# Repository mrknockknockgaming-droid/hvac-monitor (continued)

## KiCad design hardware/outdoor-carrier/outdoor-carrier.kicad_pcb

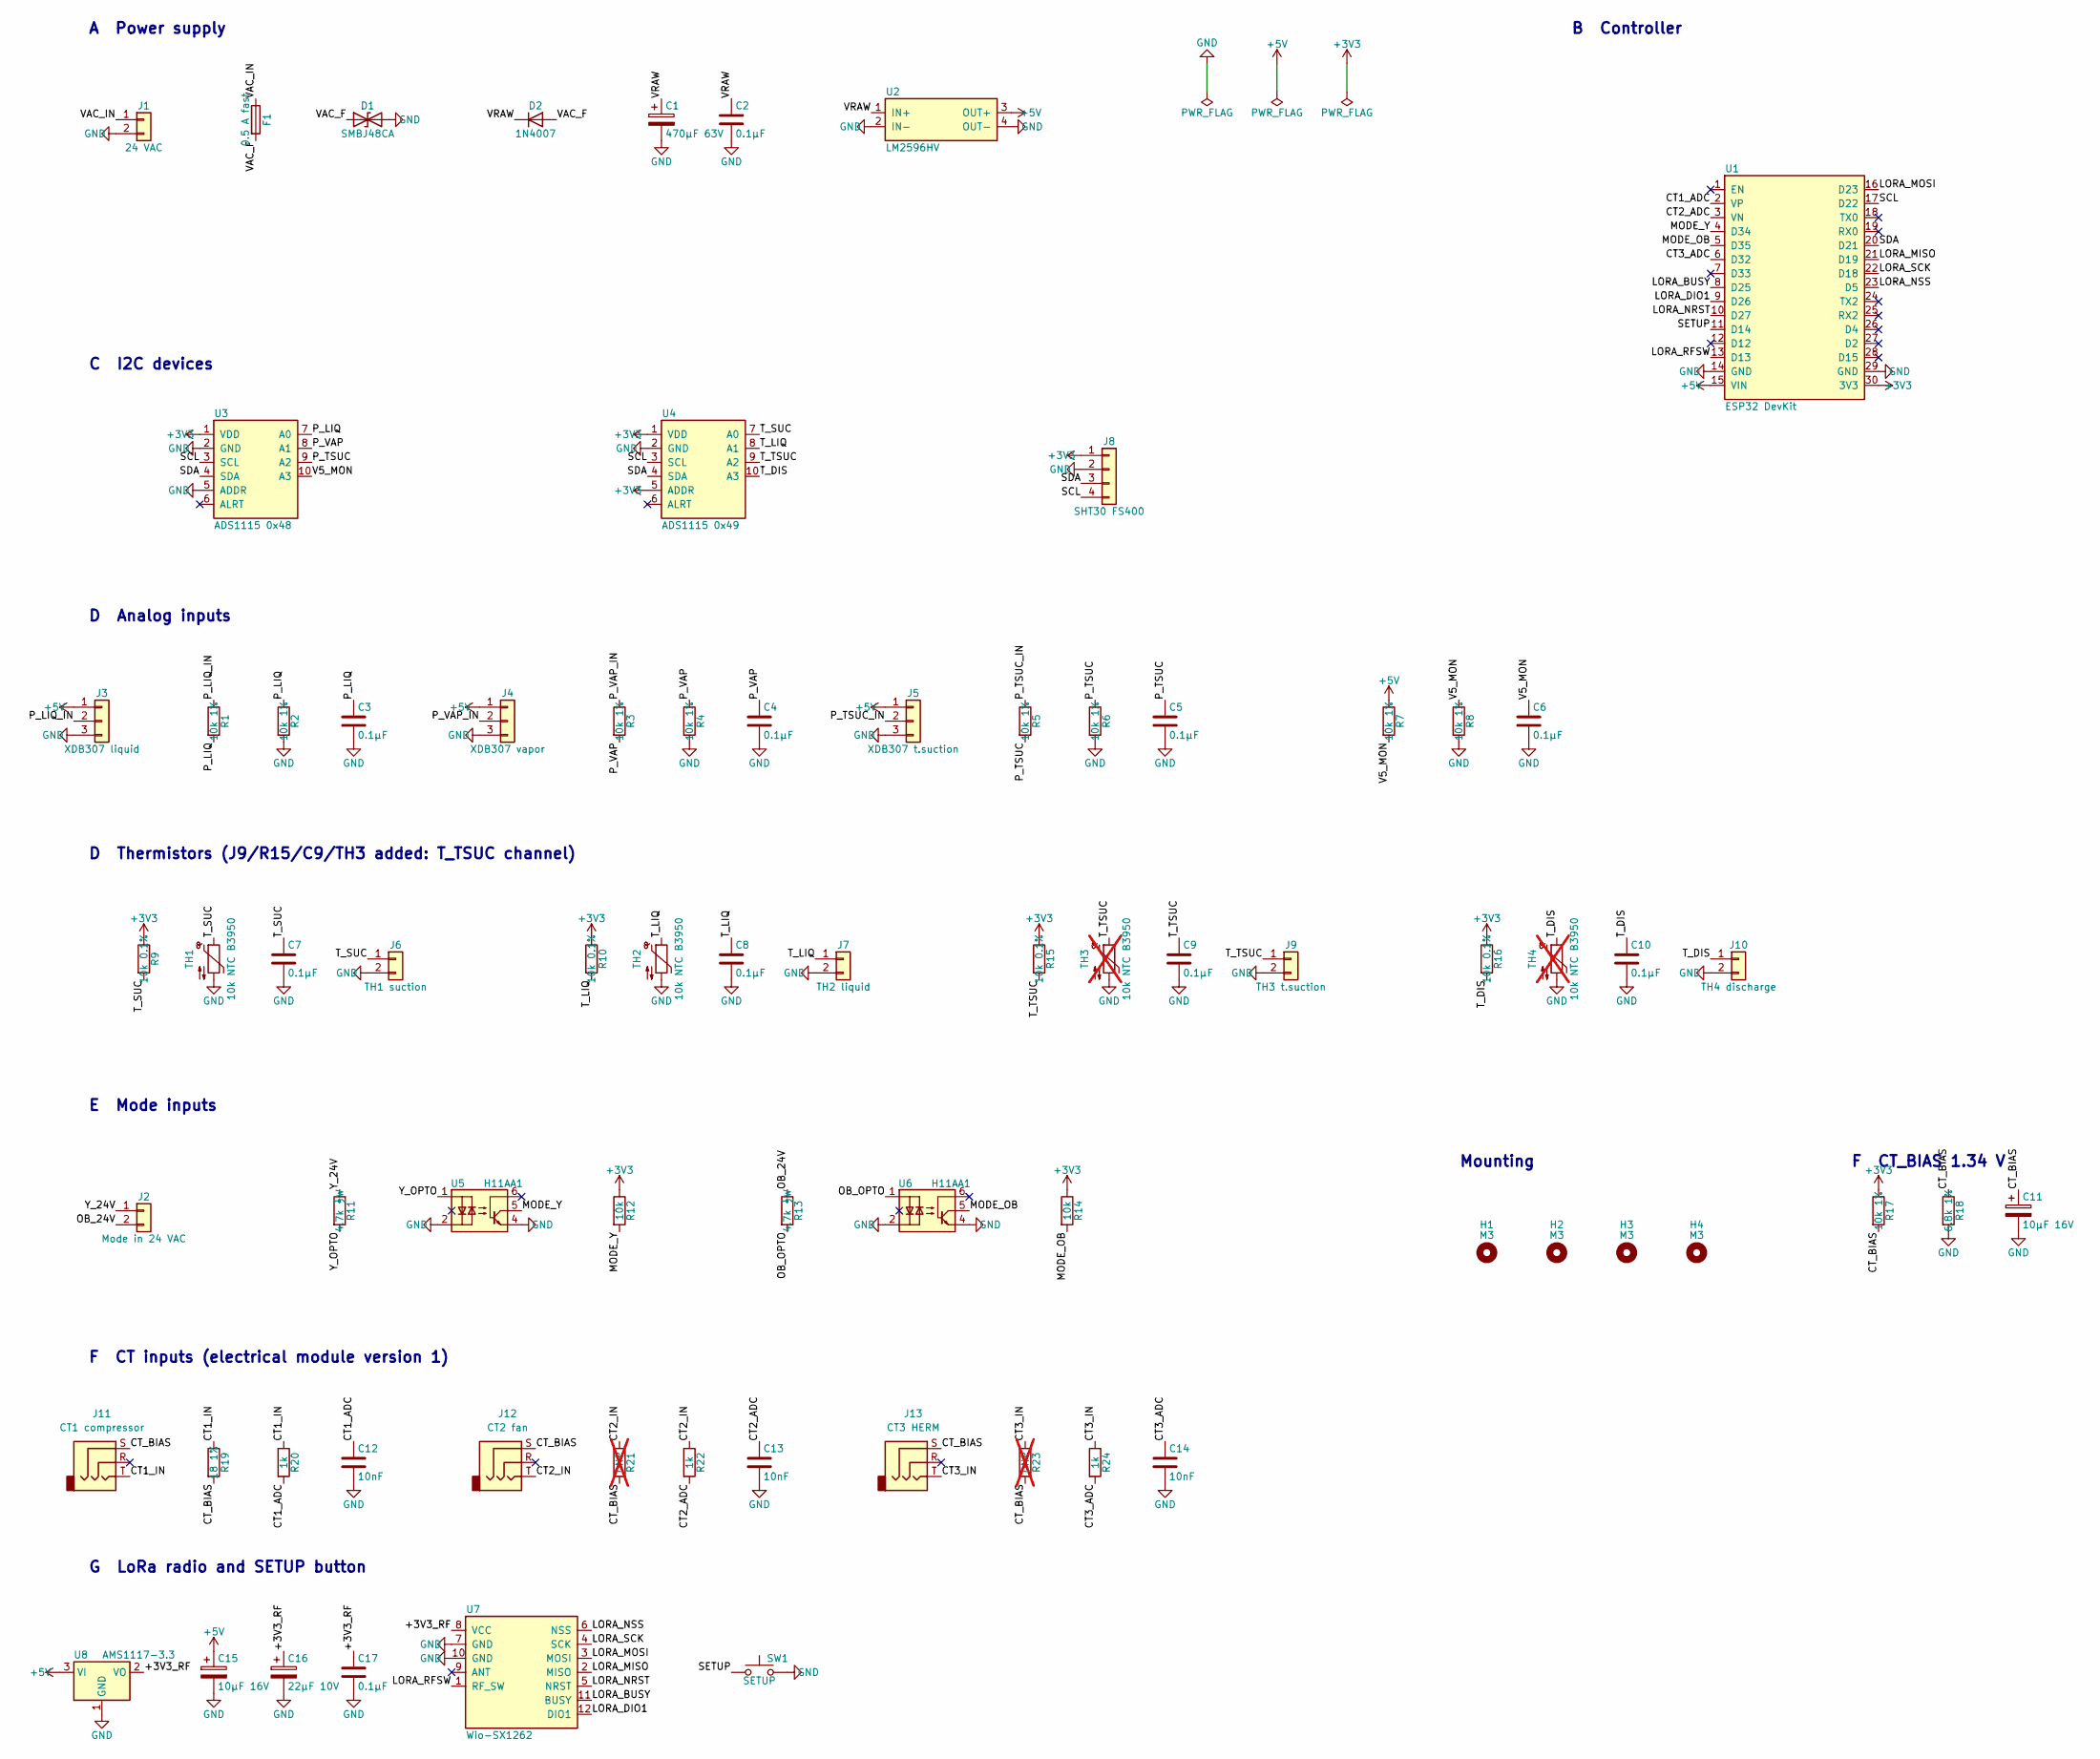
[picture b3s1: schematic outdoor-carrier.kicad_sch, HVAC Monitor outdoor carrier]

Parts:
C1: 470µF 63V; CP_Radial_D10.0mm_P5.00mm
C2, C3, C4, C5, C6, C7, C8, C9, C10, C17: 0.1µF; C_Disc_D5.0mm_W2.5mm_P2.50mm
C11, C15: 10µF 16V; CP_Radial_D5.0mm_P2.00mm
C12, C13, C14: 10nF; C_0805_2012Metric_Pad1.18x1.45mm_HandSolder
C16: 22µF 10V; CP_Radial_D5.0mm_P2.00mm
D1: SMBJ48CA; D_SMB_Handsoldering
D2: 1N4007; D_DO-41_SOD81_P10.16mm_Horizontal
F1: 0.5 A fast; Fuseholder_Clip-5x20mm_Littelfuse_111_Inline_P20.00x5.00mm_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
H1, H2, H3, H4: M3; MountingHole_3.2mm_M3_DIN965
J1: 24 VAC; PhoenixContact_MC_1,5_2-G-5.08_1x02_P5.08mm_Horizontal
J2: Mode in 24 VAC; PhoenixContact_MC_1,5_2-G-5.08_1x02_P5.08mm_Horizontal
J3: XDB307 liquid; JST_XH_B3B-XH-A_1x03_P2.50mm_Vertical
J4: XDB307 vapor; JST_XH_B3B-XH-A_1x03_P2.50mm_Vertical
J5: XDB307 t.suction; JST_XH_B3B-XH-A_1x03_P2.50mm_Vertical
J6: TH1 suction; JST_XH_B2B-XH-A_1x02_P2.50mm_Vertical
J7: TH2 liquid; JST_XH_B2B-XH-A_1x02_P2.50mm_Vertical
J8: SHT30 FS400; PhoenixContact_MC_1,5_4-G-5.08_1x04_P5.08mm_Horizontal
J9: TH3 t.suction; JST_XH_B2B-XH-A_1x02_P2.50mm_Vertical
J10: TH4 discharge; JST_XH_B2B-XH-A_1x02_P2.50mm_Vertical
J11: CT1 compressor; Jack_3.5mm_CUI_SJ1-3523N_Horizontal_EdgeTrim
J12: CT2 fan; Jack_3.5mm_CUI_SJ1-3523N_Horizontal_EdgeTrim
J13: CT3 HERM; Jack_3.5mm_CUI_SJ1-3523N_Horizontal_EdgeTrim
R1, R2, R3, R4, R5, R6, R7, R8: 10k 1%; R_Axial_DIN0207_L6.3mm_D2.5mm_P10.16mm_Horizontal
R9, R10, R15, R16: 10k 0.1%; R_Axial_DIN0207_L6.3mm_D2.5mm_P10.16mm_Horizontal
R11, R13: 4.7k ½W; R_Axial_DIN0309_L9.0mm_D3.2mm_P12.70mm_Horizontal
R12, R14: 10k; R_Axial_DIN0207_L6.3mm_D2.5mm_P10.16mm_Horizontal
R17: 10k 1%; R_0805_2012Metric_Pad1.20x1.40mm_HandSolder
R18: 6.8k 1%; R_0805_2012Metric_Pad1.20x1.40mm_HandSolder
R19: 18 1%; R_0805_2012Metric_Pad1.20x1.40mm_HandSolder
R20, R22, R24: 1k; R_0805_2012Metric_Pad1.20x1.40mm_HandSolder
R21, R23: DNP; R_0805_2012Metric_Pad1.20x1.40mm_HandSolder; not fitted
SW1: SETUP; SW_PUSH_6mm
TH1, TH2: 10k NTC B3950
TH3, TH4: 10k NTC B3950; not fitted
U1: ESP32 DevKit; ESP32_DevKit_30pin_W25.4mm
U2: LM2596HV; LM2596HVS_Module
U3: ADS1115 0x48; ADS1115_Module
U4: ADS1115 0x49; ADS1115_Module
U5, U6: H11AA1; DIP-6_W7.62mm_Socket
U7: Wio-SX1262; Wio_SX1262
U8: AMS1117-3.3; SOT-223-3_TabPin2

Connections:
+3V3: J8.1, R9.1, R10.1, R12.1, R14.1, R15.1, R16.1, R17.1, U1.30 (3V3), U3.1 (VDD), U4.1 (VDD), U4.5 (ADDR)
+5V: C15.1, J3.1, J4.1, J5.1, R7.1, U1.15 (VIN), U2.3 (OUT+), U8.3 (VI)
/+3V3_RF: C16.1, C17.1, U7.8 (VCC), U8.2 (VO)
/CT1_ADC: C12.1, R20.2, U1.2 (VP)
/CT1_IN: J11.T, R19.1, R20.1
/CT2_ADC: C13.1, R22.2, U1.3 (VN)
/CT2_IN: J12.T, R21.1, R22.1
/CT3_ADC: C14.1, R24.2, U1.6 (D32)
/CT3_IN: J13.T, R23.1, R24.1
/CT_BIAS: C11.1, J11.S, J12.S, J13.S, R17.2, R18.1, R19.2, R21.2, R23.2
/LORA_BUSY: U1.8 (D25), U7.11 (BUSY)
/LORA_DIO1: U1.9 (D26), U7.12 (DIO1)
/LORA_MISO: U1.21 (D19), U7.2 (MISO)
/LORA_MOSI: U1.16 (D23), U7.3 (MOSI)
/LORA_NRST: U1.10 (D27), U7.5 (NRST)
/LORA_NSS: U1.23 (D5), U7.6 (NSS)
/LORA_RFSW: U1.13 (D13), U7.1 (RF_SW)
/LORA_SCK: U1.22 (D18), U7.4 (SCK)
/MODE_OB: R14.2, U1.5 (D35), U6.5
/MODE_Y: R12.2, U1.4 (D34), U5.5
/OB_24V: J2.2, R13.1
/OB_OPTO: R13.2, U6.1
/P_LIQ: C3.1, R1.2, R2.1, U3.7 (A0)
/P_LIQ_IN: J3.2, R1.1
/P_TSUC: C5.1, R5.2, R6.1, U3.9 (A2)
/P_TSUC_IN: J5.2, R5.1
/P_VAP: C4.1, R3.2, R4.1, U3.8 (A1)
/P_VAP_IN: J4.2, R3.1
/SCL: J8.4, U1.17 (D22), U3.3 (SCL), U4.3 (SCL)
/SDA: J8.3, U1.20 (D21), U3.4 (SDA), U4.4 (SDA)
/SETUP: SW1.1, U1.11 (D14)
/T_DIS: C10.1, J10.1, R16.2, TH4.1, U4.10 (A3)
/T_LIQ: C8.1, J7.1, R10.2, TH2.1, U4.8 (A1)
/T_SUC: C7.1, J6.1, R9.2, TH1.1, U4.7 (A0)
/T_TSUC: C9.1, J9.1, R15.2, TH3.1, U4.9 (A2)
/V5_MON: C6.1, R7.2, R8.1, U3.10 (A3)
/VAC_F: D1.1 (A1), D2.2 (A), F1.2
/VAC_IN: F1.1, J1.1
/VRAW: C1.1, C2.1, D2.1 (K), U2.1 (IN+)
/Y_24V: J2.1, R11.1
/Y_OPTO: R11.2, U5.1
GND: C1.2, C2.2, C3.2, C4.2, C5.2, C6.2, C7.2, C8.2, C9.2, C10.2, C11.2, C12.2, C13.2, C14.2, C15.2, C16.2, C17.2, D1.2 (A2), J1.2, J3.3, J4.3, J5.3, J6.2, J7.2, J8.2, J9.2, J10.2, R2.2, R4.2, R6.2, R8.2, R18.2, SW1.2, TH1.2, TH2.2, TH3.2, TH4.2, U1.14 (GND), U1.29 (GND), U2.2 (IN−), U2.4 (OUT−), U3.2 (GND), U3.5 (ADDR), U4.2 (GND), U5.2, U5.4, U6.2, U6.4, U7.7 (GND), U7.10 (GND), U8.1 (GND)

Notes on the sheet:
A Power supply
B Controller
C I2C devices
D Analog inputs
D Thermistors (J9/R15/C9/TH3 added: T_TSUC channel)
E Mode inputs
Mounting
F CT inputs (electrical module version 1)
F CT_BIAS 1.34 V
G LoRa radio and SETUP button

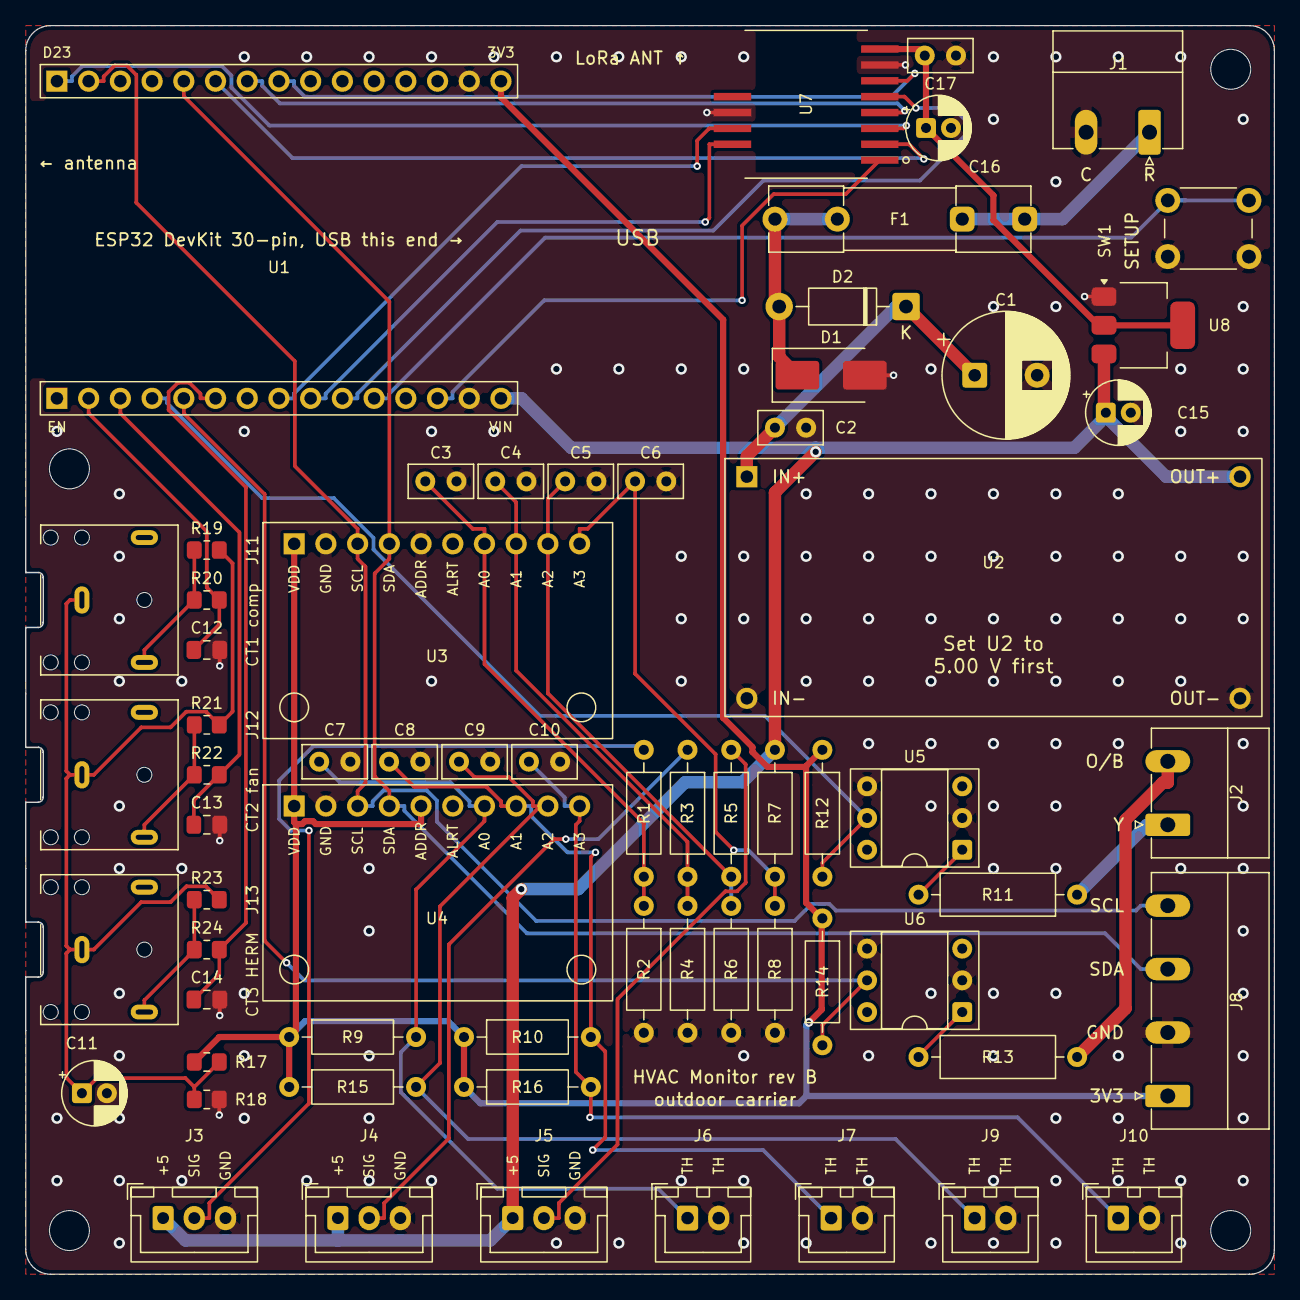
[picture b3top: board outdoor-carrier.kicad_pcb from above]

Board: 2 copper layers, 100.0 x 100.0 mm, 70 parts (0 on the bottom side), 42 nets.

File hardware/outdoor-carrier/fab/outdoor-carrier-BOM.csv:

"Refs","Value","Footprint","Qty","DNP","Off-board"
"C1","470µF 63V","Capacitor_THT:CP_Radial_D10.0mm_P5.00mm","1","",""
"C2-C10,C17","0.1µF","Capacitor_THT:C_Disc_D5.0mm_W2.5mm_P2.50mm","10","",""
"C11,C15","10µF 16V","Capacitor_THT:CP_Radial_D5.0mm_P2.00mm","2","",""
"C12-C14","10nF","Capacitor_SMD:C_0805_2012Metric_Pad1.18x1.45mm_HandSolder","3","",""
"C16","22µF 10V","Capacitor_THT:CP_Radial_D5.0mm_P2.00mm","1","",""
"D1","SMBJ48CA","Diode_SMD:D_SMB_Handsoldering","1","",""
"D2","1N4007","Diode_THT:D_DO-41_SOD81_P10.16mm_Horizontal","1","",""
"F1","0.5 A fast","Fuse:Fuseholder_Clip-5x20mm_Littelfuse_111_Inline_P20.00x5.00mm_D1.05mm_Horizontal","1","",""
"J1","24 VAC","Connector_Phoenix_MC_HighVoltage:PhoenixContact_MC_1,5_2-G-5.08_1x02_P5.08mm_Horizontal","1","",""
"J2","Mode in 24 VAC","Connector_Phoenix_MC_HighVoltage:PhoenixContact_MC_1,5_2-G-5.08_1x02_P5.08mm_Horizontal","1","",""
"J3","XDB307 liquid","Connector_JST:JST_XH_B3B-XH-A_1x03_P2.50mm_Vertical","1","",""
"J4","XDB307 vapor","Connector_JST:JST_XH_B3B-XH-A_1x03_P2.50mm_Vertical","1","",""
"J5","XDB307 t.suction","Connector_JST:JST_XH_B3B-XH-A_1x03_P2.50mm_Vertical","1","",""
"J6","TH1 suction","Connector_JST:JST_XH_B2B-XH-A_1x02_P2.50mm_Vertical","1","",""
"J7","TH2 liquid","Connector_JST:JST_XH_B2B-XH-A_1x02_P2.50mm_Vertical","1","",""
"J8","SHT30 FS400","Connector_Phoenix_MC_HighVoltage:PhoenixContact_MC_1,5_4-G-5.08_1x04_P5.08mm_Horizontal","1","",""
"J9","TH3 t.suction","Connector_JST:JST_XH_B2B-XH-A_1x02_P2.50mm_Vertical","1","",""
"J10","TH4 discharge","Connector_JST:JST_XH_B2B-XH-A_1x02_P2.50mm_Vertical","1","",""
"J11","CT1 compressor","hvac_carrier:Jack_3.5mm_CUI_SJ1-3523N_Horizontal_EdgeTrim","1","",""
"J12","CT2 fan","hvac_carrier:Jack_3.5mm_CUI_SJ1-3523N_Horizontal_EdgeTrim","1","",""
"J13","CT3 HERM","hvac_carrier:Jack_3.5mm_CUI_SJ1-3523N_Horizontal_EdgeTrim","1","",""
"R1-R8","10k 1%","Resistor_THT:R_Axial_DIN0207_L6.3mm_D2.5mm_P10.16mm_Horizontal","8","",""
"R9,R10,R15,R16","10k 0.1%","Resistor_THT:R_Axial_DIN0207_L6.3mm_D2.5mm_P10.16mm_Horizontal","4","",""
"R11,R13","4.7k ½W","Resistor_THT:R_Axial_DIN0309_L9.0mm_D3.2mm_P12.70mm_Horizontal","2","",""
"R12,R14","10k","Resistor_THT:R_Axial_DIN0207_L6.3mm_D2.5mm_P10.16mm_Horizontal","2","",""
"R17","10k 1%","Resistor_SMD:R_0805_2012Metric_Pad1.20x1.40mm_HandSolder","1","",""
"R18","6.8k 1%","Resistor_SMD:R_0805_2012Metric_Pad1.20x1.40mm_HandSolder","1","",""
"R19","18 1%","Resistor_SMD:R_0805_2012Metric_Pad1.20x1.40mm_HandSolder","1","",""
"R20,R22,R24","1k","Resistor_SMD:R_0805_2012Metric_Pad1.20x1.40mm_HandSolder","3","",""
"R21,R23","DNP","Resistor_SMD:R_0805_2012Metric_Pad1.20x1.40mm_HandSolder","2","DNP",""
"SW1","SETUP","Button_Switch_THT:SW_PUSH_6mm","1","",""
"TH1,TH2","10k NTC B3950","","2","","Excluded from board"
"TH3,TH4","10k NTC B3950","","2","DNP","Excluded from board"
"U1","ESP32 DevKit","hvac_carrier:ESP32_DevKit_30pin_W25.4mm","1","",""
"U2","LM2596HV","hvac_carrier:LM2596HVS_Module","1","",""
"U3","ADS1115 0x48","hvac_carrier:ADS1115_Module","1","",""
"U4","ADS1115 0x49","hvac_carrier:ADS1115_Module","1","",""
"U5,U6","H11AA1","Package_DIP:DIP-6_W7.62mm_Socket","2","",""
"U7","Wio-SX1262","hvac_carrier:Wio_SX1262","1","",""
"U8","AMS1117-3.3","Package_TO_SOT_SMD:SOT-223-3_TabPin2","1","",""

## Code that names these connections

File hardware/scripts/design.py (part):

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    J10 + R16 + C10: discharge-line thermistor on T_DIS (ADS 0x49 A3, firmware t_dis).
    Three CT inputs (electrical module version 1) on 3.5 mm jacks for SCT-013 clamps:
    CT1 compressor common (VP), CT2 condenser fan (VN), CT3 HERM lead (D32), each with a
    burden footprint, 1k + 10 nF to the ADC pin, sleeves on a shared CT_BIAS (~1.34 V).
  * Indoor: TCA9548A mux (U7, 0x70) on the board with JST-XH 4-pin jacks for the SHT45
    return/supply (ch 0/1) and SDP810 return/supply/filter (ch 2/3/4), 10k pull-ups per
    channel. J5 stays as the main-bus I2C terminal, now fitted.
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    """Rev A zone A, identical on both boards."""
    return [
        part('J1', 'Connector_Generic:Conn_01x02', '24 VAC', fp_term(2), 30.48, y0,
             {'1': 'VAC_IN', '2': 'GND'}, pinlabels=['R', 'C']),
        part('F1', 'Device:Fuse', '0.5 A fast', FP_FUSE, 50.8, y0,
             {'1': 'VAC_IN', '2': 'VAC_F'}),
        part('D1', 'Device:D_TVS', 'SMBJ48CA', FP_D1, 71.12, y0,
             {'1': 'VAC_F', '2': 'GND'}),
        part('D2', 'Device:D', '1N4007', FP_D2, 101.6, y0,
             {'1': 'VRAW', '2': 'VAC_F'}),  # pin 1 = K, pin 2 = A
        part('C1', 'Device:C_Polarized', '470µF 63V', FP_C1, 124.46, y0,
             {'1': 'VRAW', '2': 'GND'}),
        part('C2', 'Device:C', '0.1µF', FP_C_DISC, 137.16, y0,
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                 in_bom=False) for i in range(1, 5)]


LORA_PINS = dict(D5='LORA_NSS', D18='LORA_SCK', D19='LORA_MISO', D23='LORA_MOSI',
                 D26='LORA_DIO1', D27='LORA_NRST', D25='LORA_BUSY', D13='LORA_RFSW', D14='SETUP')


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    p += ct_input('J13', 'R23', 'R24', 'C14', 3, 'HERM', 'CT3_ADC', 'DNP', 170.18, 281.94)
    p += lora_section('U7', 'U8', 'C15', 'C16', 'C17', 'SW1', 22.86, 320.04)
    p.append(part('J2', 'Connector_Generic:Conn_01x02', 'Mode in 24 VAC', fp_term(2),
                  30.48, 236.22, {'1': 'Y_24V', '2': 'OB_24V'}, pinlabels=['Y', 'O/B']))
    p += opto('R11', 'U5', 'R12', 'Y', 66.04, 236.22)
    p += opto('R13', 'U6', 'R14', 'OB', 147.32, 236.22)
    p += mounting_holes(274.32, 243.84)
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#   * MCP23017 (0x20): six PhotoMOS outputs Y1 Y2 W1 W2 G O/B, six H11AA1 read-backs, the
#     TPS3823 watchdog input. The TPS3823 resets the MCP23017 if the firmware stops toggling WDI,
#     which turns every output off (the display board's EN isn't brought out).
#   * SC18IS602B I2C-to-SPI bridge (0x28) for the Wio-SX1262: SS0 = NSS, GPIO1 = BUSY (input),
#     GPIO2 = NRST, GPIO3 = RF_SW. DIO1 goes to the display's GPIO6 (sensor header) for the
#     receive interrupt; without that wire the firmware polls the radio's IRQ flags.
#   * SHT45 room sensor on a Qwiic cable (thermally isolated tab, away from the display heat).
# Rev A stacks under the display (2026-10-30): same 106 x 68 mm outline as the Waveshare board,
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def thermostat():
    p = [
        part('J1', 'Connector_Generic:Conn_01x03', '24 VAC', fp_mcv(3), 30.48, 38.1,
             {'1': 'RH_24V', '2': 'RC_24V', '3': 'GND'}, pinlabels=['Rh', 'Rc', 'C']),
        part('JP1', 'Jumper:Jumper_2_Open', 'Rc=Rh', fp_hdr(2), 30.48, 55.88,
             {'1': 'RC_24V', '2': 'RH_24V'}),
        part('F1', 'Device:Fuse', '0.5 A fast 63 V', FP_F1206, 50.8, 38.1, {'1': 'RC_24V', '2': 'VAC_F'}),
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
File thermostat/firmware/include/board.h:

// Waveshare ESP32-S3-Touch-LCD-4.3 plus the thermostat's output board (thermostat/README.md).
// Pin numbers for the display come from Waveshare's documentation for this board:
// CHECK THEM against the board's schematic before the first power-up.
#pragma once
#include <Arduino.h>

constexpr const char* FW_VERSION = "0.1.0";

// ---- shared I2C bus (touch, CH422G, and our parts on the header)
constexpr int PIN_I2C_SDA = 8;
constexpr int PIN_I2C_SCL = 9;
constexpr int PIN_TOUCH_INT = 4;

// ---- RGB panel (800 x 480, RGB565)
constexpr int LCD_W = 800, LCD_H = 480;
constexpr int PIN_LCD_DE = 5, PIN_LCD_VSYNC = 3, PIN_LCD_HSYNC = 46, PIN_LCD_PCLK = 7;
constexpr int PIN_LCD_B[5] = {14, 38, 18, 17, 10};      // B3..B7
constexpr int PIN_LCD_G[6] = {39, 0, 45, 48, 47, 21};   // G2..G7
constexpr int PIN_LCD_R[5] = {1, 2, 42, 41, 40};        // R3..R7
constexpr uint32_t LCD_PCLK_HZ = 14000000;

// ---- CH422G I/O expander on the board (backlight, panel and touch resets)
constexpr uint8_t CH422G_MODE = 0x24;   // write 0x01: IO0-7 are outputs
constexpr uint8_t CH422G_OUT = 0x38;    // output latch
constexpr uint8_t EXIO_TP_RST = 1 << 1, EXIO_LCD_BL = 1 << 2, EXIO_LCD_RST = 1 << 3, EXIO_SD_CS = 1 << 4;

// ---- GT911 touch controller (address chosen at reset by the INT pin: low -> 0x5D)
constexpr uint8_t GT911_ADDR = 0x5D, GT911_ADDR_ALT = 0x14;

// ---- our carrier board (hardware/thermostat-carrier, hardware/scripts/design.py), on the same
// I2C bus through the display's I2C header; the sensor header's GPIO6 carries the radio's DIO1.
// MCP23017 (0x20): GPA0 Y1, GPA1 Y2, GPA2 W1, GPA3 W2, GPA4 G, GPA5 O/B -> PhotoMOS LEDs (high = on),
//                  GPA6 -> TPS3823 WDI (toggled every loop), GPA7 spare (output-only pin);
//                  GPB0-5 <- H11AA1 read-back (low while 24 VAC is on the terminal): Y1, Y2, W1, G,
//                  O/B, W2. GPB6 spare, GPB7 output-only.
// The TPS3823's RESET drives the MCP23017's RESET (the display board's EN isn't brought out): if
// the firmware stops toggling WDI, the expander resets to all inputs and every output turns off.
constexpr uint8_t MCP_ADDR = 0x20;
constexpr uint8_t OUT_Y = 0, OUT_Y2 = 1, OUT_W = 2, OUT_W2 = 3, OUT_G = 4, OUT_OB = 5, OUT_WDI = 6;
constexpr uint8_t SENSE_Y = 0, SENSE_Y2 = 1, SENSE_W = 2, SENSE_G = 3, SENSE_OB = 4, SENSE_W2 = 5;
constexpr uint8_t SENSE_MASK = 0x3F;

// ---- LoRa (Wio-SX1262) behind the SC18IS602B I2C-to-SPI bridge (0x28, A0-A2 low): SS0 = NSS,
// GPIO1 = BUSY, GPIO2 = NRST, GPIO3 = RF_SW (sc18is602_hal.h numbers them from BRIDGE_PIN).
constexpr uint8_t LORA_BRIDGE_ADDR = 0x28;
constexpr int LORA_BRIDGE_NSS = 0x100, LORA_BRIDGE_BUSY = 0x101, LORA_BRIDGE_NRST = 0x102,
              LORA_BRIDGE_RFSW = 0x103;
constexpr int LORA_DIO1_GPIO = 6;       // display board sensor header (check against Waveshare's schematic)

// ---- room sensor: SHT45 (0x44) on its thermally isolated tab
constexpr uint8_t SHT45_ADDR = 0x44;
constexpr float ROOM_OFFSET_F = 0.0f;   // calibrate against a reference: the display warms the case
